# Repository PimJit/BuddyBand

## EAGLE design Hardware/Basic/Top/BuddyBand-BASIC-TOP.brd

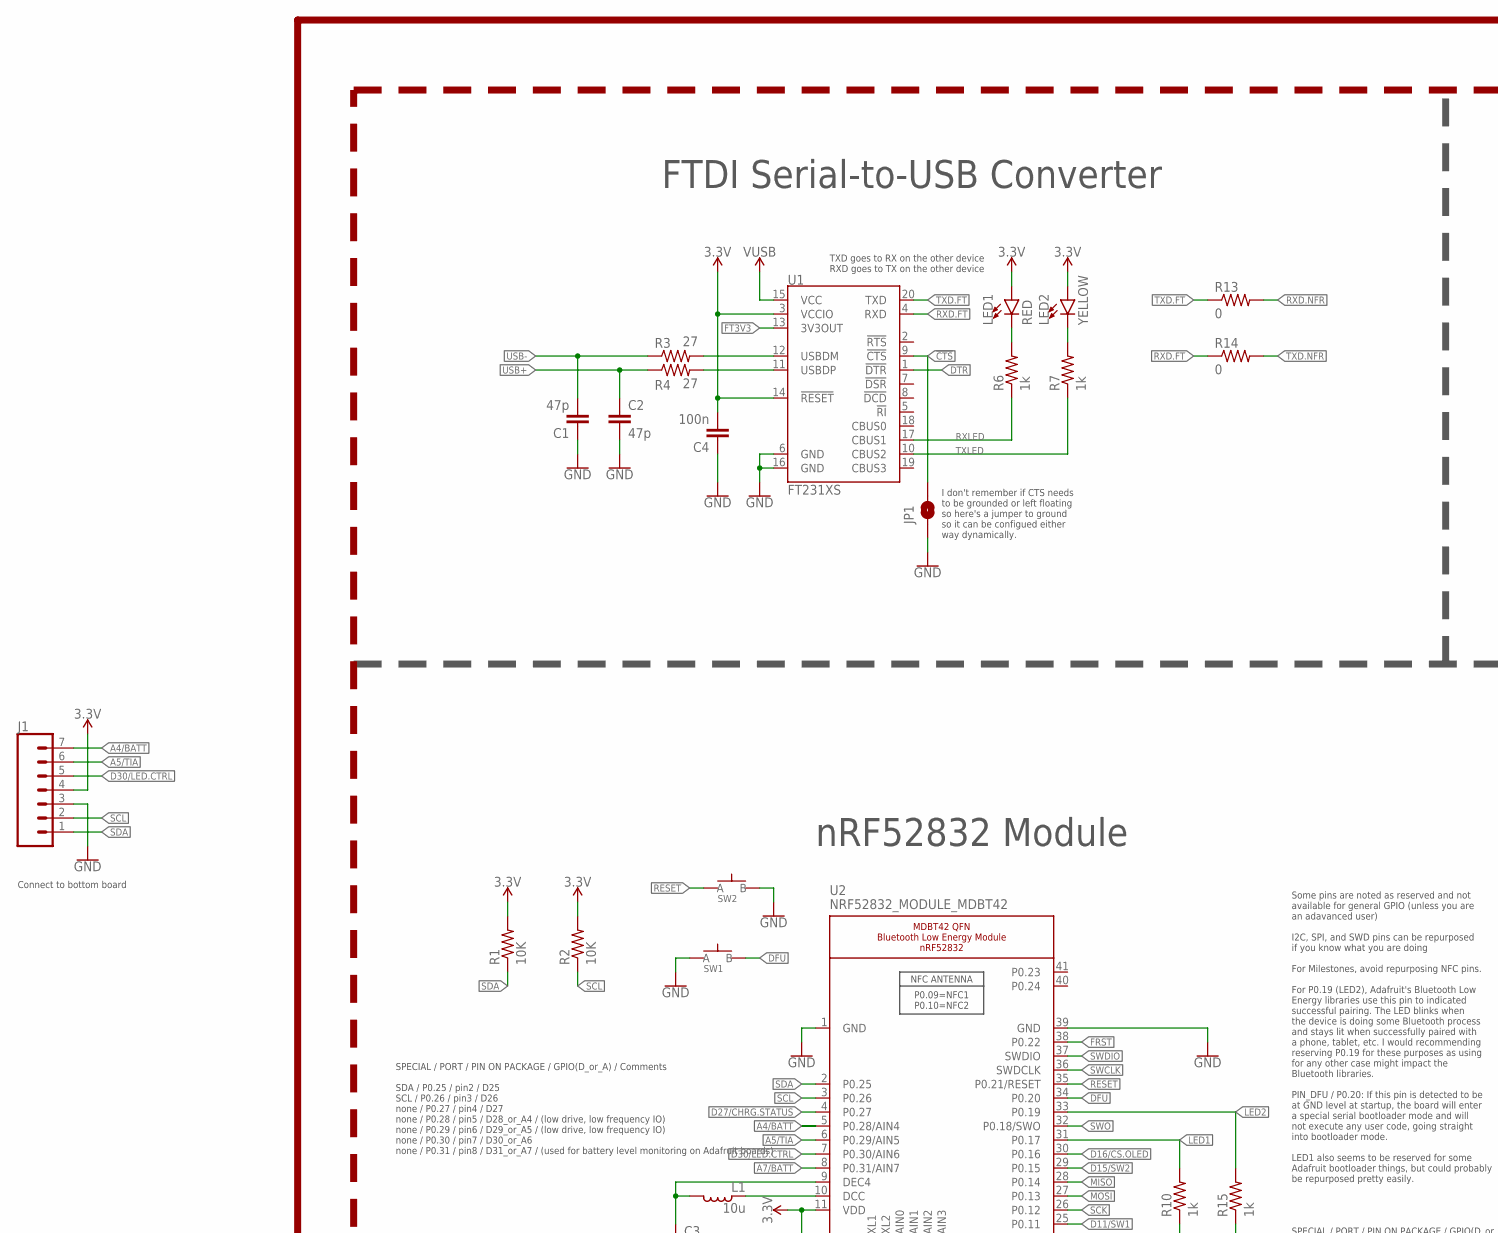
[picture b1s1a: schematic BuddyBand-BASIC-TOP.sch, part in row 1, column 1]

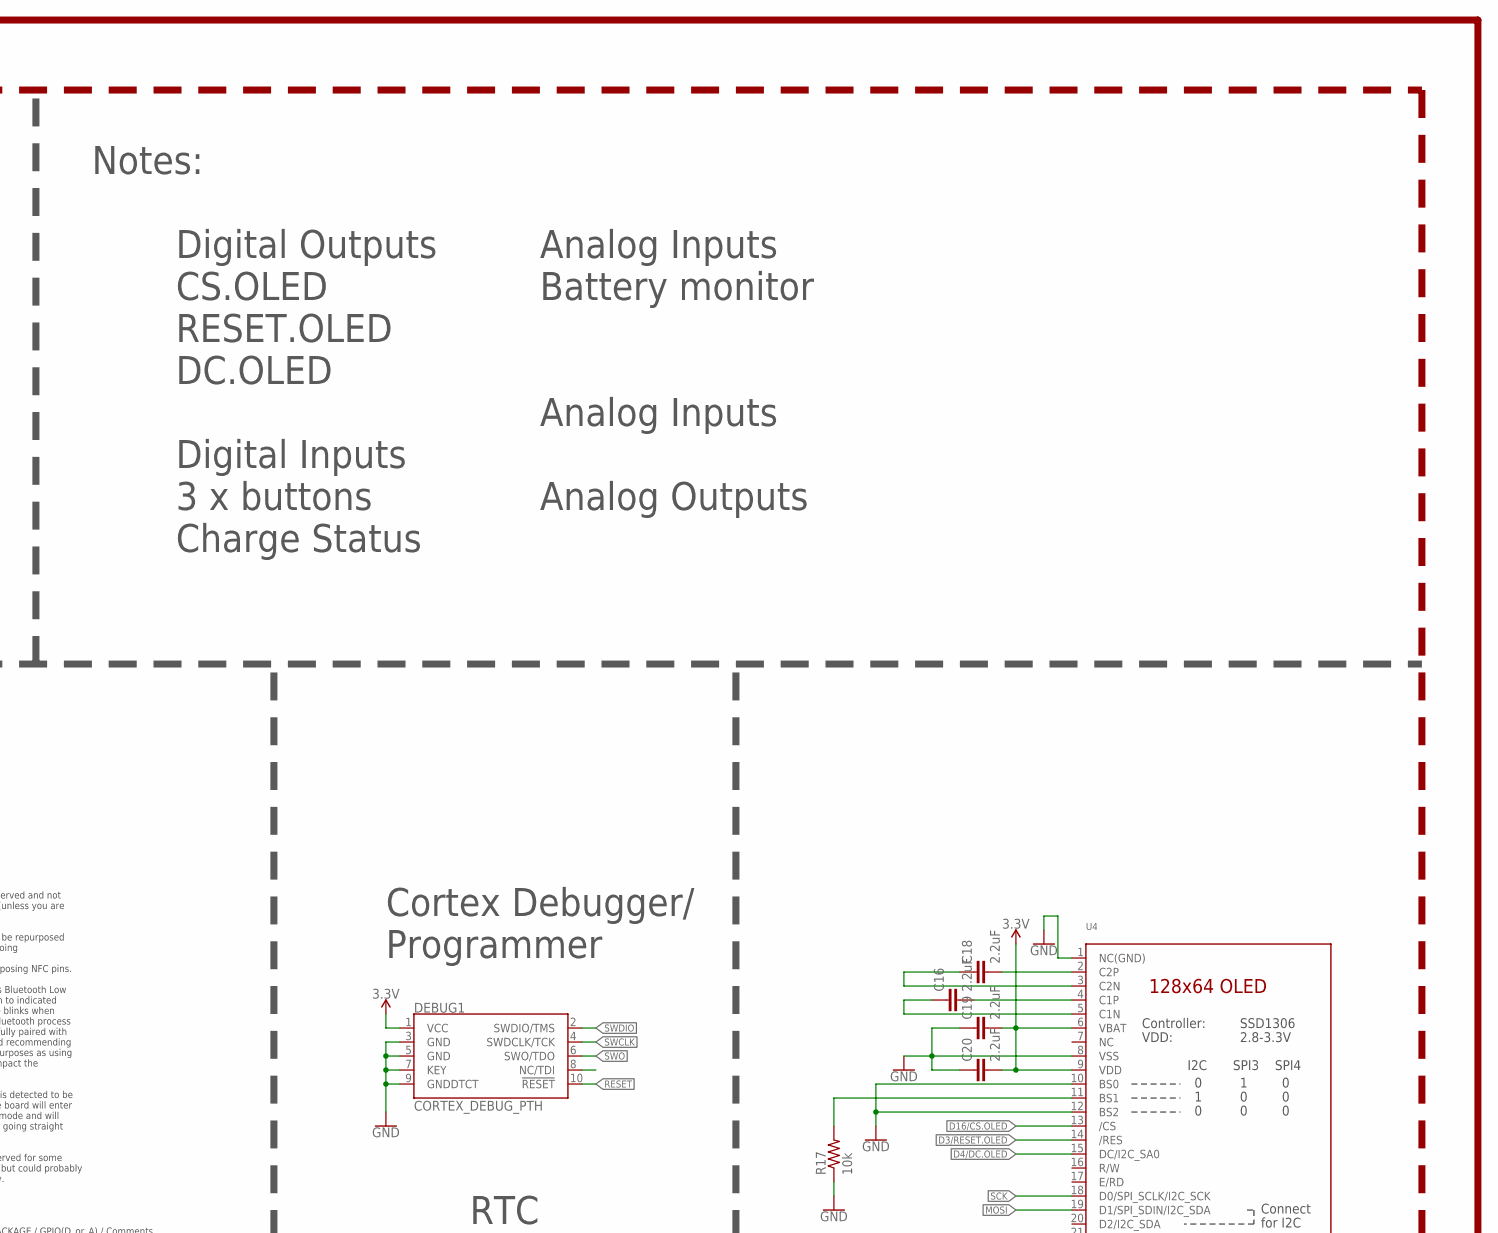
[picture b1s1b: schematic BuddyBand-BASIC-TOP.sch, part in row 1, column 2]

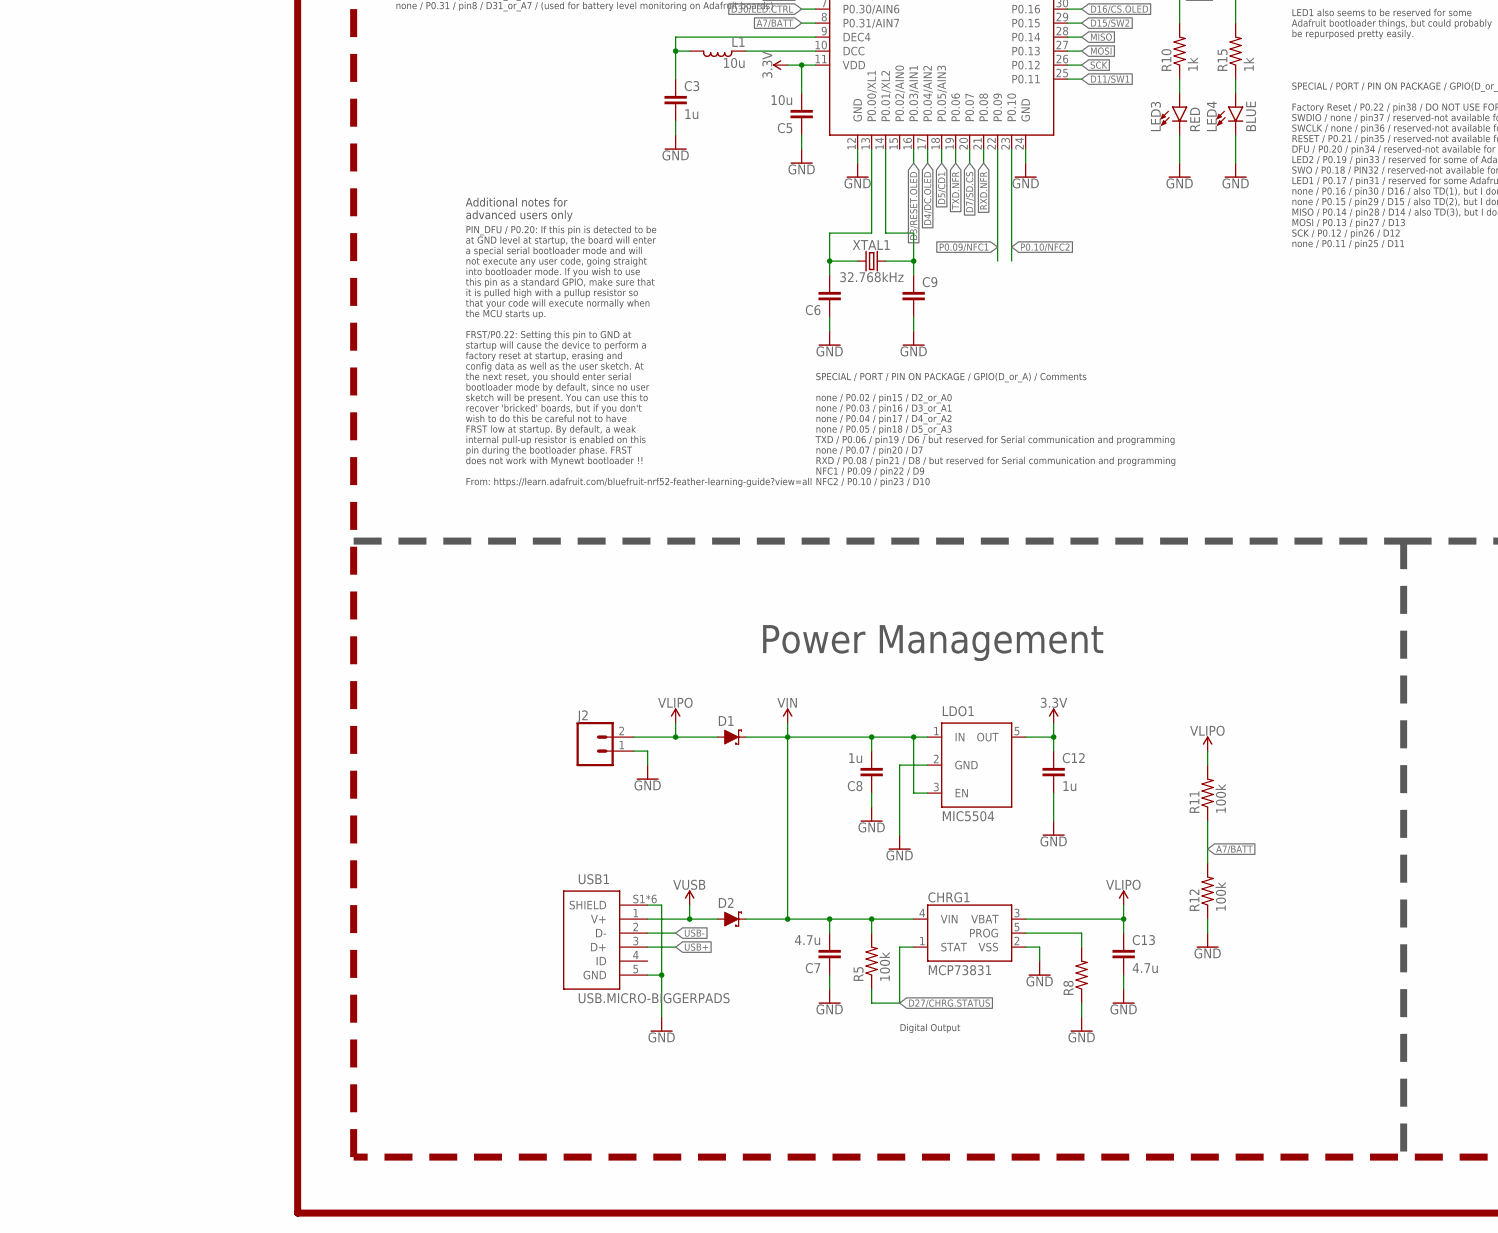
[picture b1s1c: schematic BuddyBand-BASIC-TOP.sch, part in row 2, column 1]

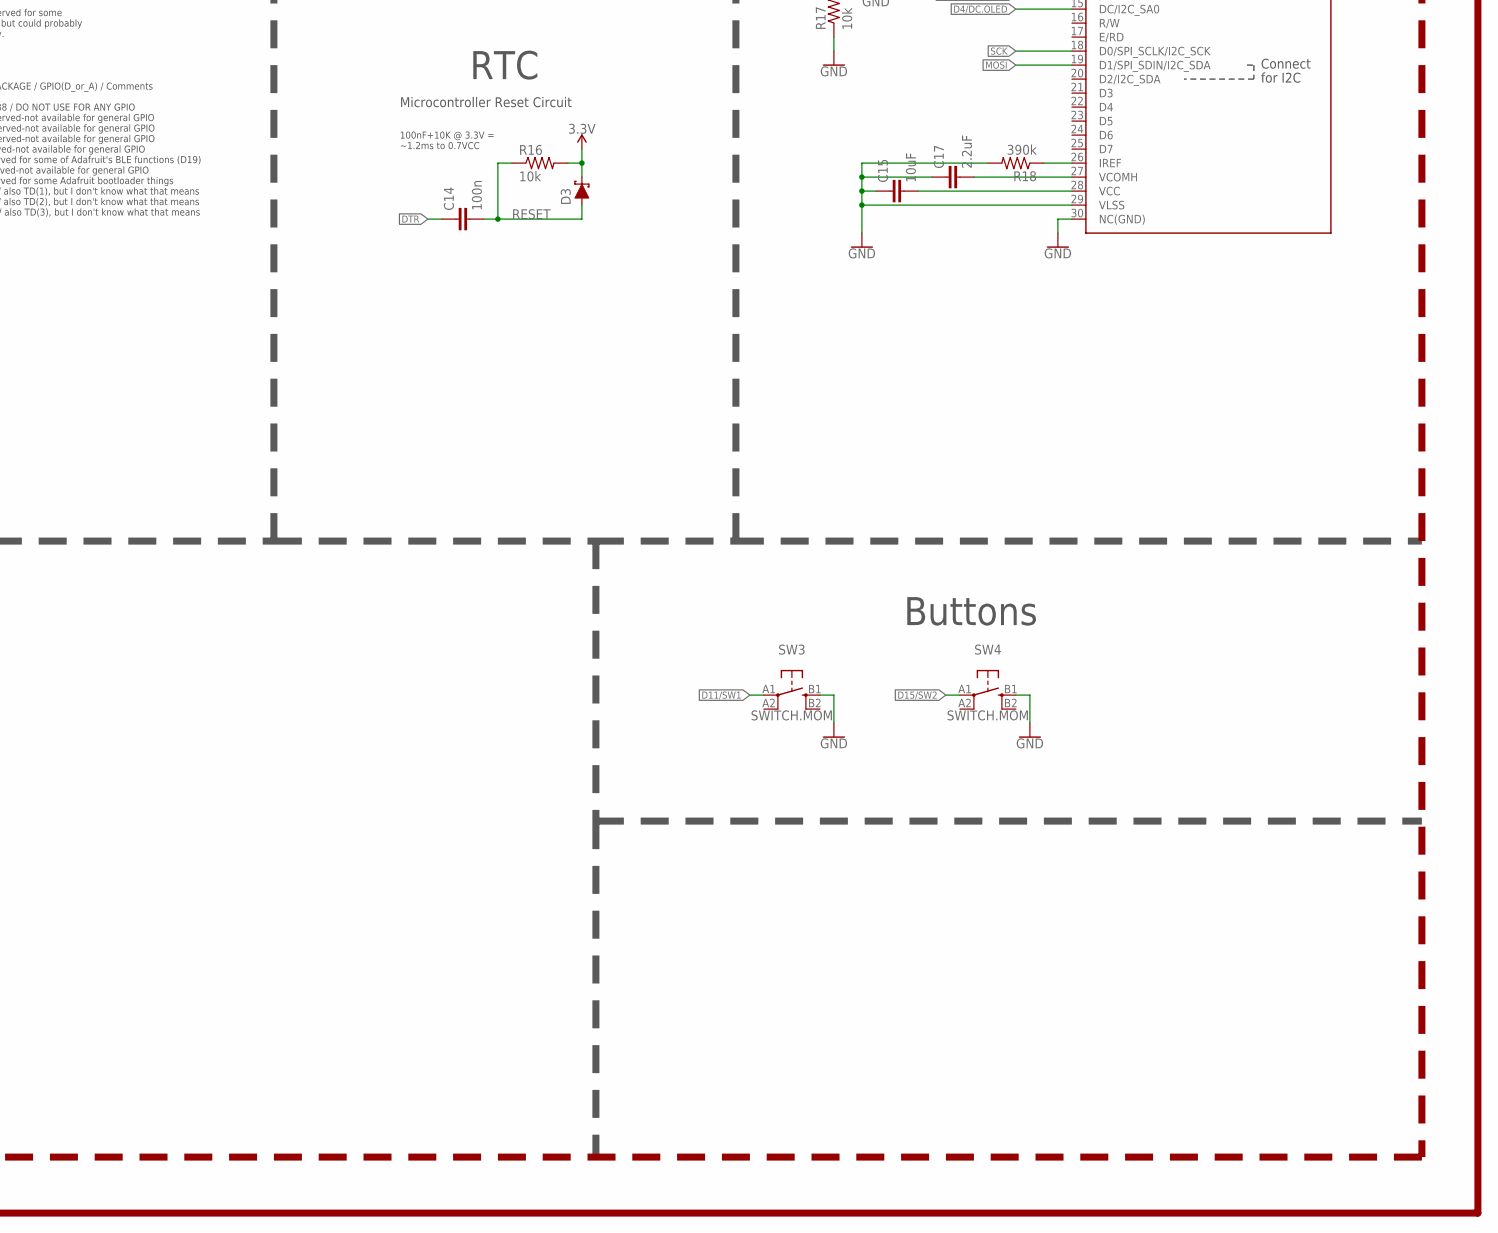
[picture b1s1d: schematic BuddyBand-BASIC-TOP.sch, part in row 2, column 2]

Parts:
C1, C2: 47p; C0603
C3, C8, C12: 1u; C0603
C4, C14: 100n; C0603
C5: 10u; C0805
C6, C9: CAPACITOR0603; C0603
C7, C13: 4.7u; C0603
C15: 10uF; C0603
C16, C17, C18, C19, C20: 2.2uF; C0402
CHRG1: MCP73831; SOT23-5
D1, D2, D3: SCHOTTKY-USC; USC
DEBUG1: CORTEX_DEBUG_PTH; 2X5-PTH-1.27MM
J1: CONN_07-1.27MM; 1X07_1.27MM
J2: CONN_02; 1X02
JP1: JUMPER-SMT_2_NO_SILK; SMT-JUMPER_2_NO_SILK
L1: 10u; L0603
LDO1: MIC5504; SOT23-5
LED1, LED3: RED; LED-0603
LED2: YELLOW; LED-0603
LED4: BLUE; LED-0603
R1, R2: 10K; R0603
R3, R4: 27; R0603
R5, R11, R12: 100k; R0603
R6, R7, R10, R15: 1k; R0603
R8: RESISTOR0603; R0603
R13, R14: 0; R0603
R16, R17: 10k; R0603
R18: 390k; R0603
SW1, SW2: SPST-PTS830GG140-COPY.1-3; BUTTON-GULLWING
SW3, SW4: SWITCH.MOM; TACTILE_SWITCH_SMD_6.2MM_TALL
U1: FT231XS; SSOP20_L
U2: NRF52832_MODULE_MDBT42; BLE_MODULE_RAYTAC_MDBT42
U4: DISP_OLED_UG-2864HSWEG01-NO-WRAPAROUND; UG-2864HSWEG01_0.96IN_NO-WRAPAROUND
USB1: USB.MICRO-BIGGERPADS; USB-MICRO-01.BIGGERPADS
XTAL1: 32.768kHz; 2-SMD.NOLEAD.2.0MMTO1.2MM

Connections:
3.3V: C4.2, C5.2, C12.1, C19.2, C20.2, D3.- (C), DEBUG1.1 (VCC), J1.4, LDO1.5 (OUT), LED1.A, LED2.A, R1.2, R2.2, R16.2, U1.3 (VCCIO), U1.14 (!RESET), U2.11 (VDD), U4.6 (VBAT), U4.9 (VDD)
!CTS: JP1.2, U1.9 (!CTS)
A4/BATT: J1.7, U2.5 (P0.28/AIN4)
A5/TIA: J1.6, U2.6 (P0.29/AIN5)
A7/BATT: R11.1, R12.2, U2.8 (P0.31/AIN7)
D3/RESET.OLED: U2.16 (P0.03/AIN1), U4.14 (/RES)
D4/DC.OLED: U2.17 (P0.04/AIN2), U4.15 (DC/I2C_SA0)
D5/CD1: U2.18 (P0.05/AIN3)
D7/SD.CS: U2.20 (P0.07)
D11/SW1: SW3.A1 (1), U2.25 (P0.11)
D15/SW2: SW4.A1 (1), U2.29 (P0.15)
D16/CS.OLED: U2.30 (P0.16), U4.13 (/CS)
D27/CHRG.STATUS: CHRG1.1 (STAT), R5.1, U2.4 (P0.27)
D30/LED.CTRL: J1.5, U2.7 (P0.30/AIN6)
DFU: SW1.3 (B), U2.34 (P0.20)
DTR: C14.1, U1.1 (!DTR)
FRST: U2.38 (P0.22)
FT3V3: U1.13 (3V3OUT)
GND: C1.1, C2.2, C3.2, C4.1, C5.1, C6.1, C7.1, C8.1, C9.2, C12.2, C13.2, C15.1, C17.1, C19.1, C20.1, CHRG1.2 (VSS), DEBUG1.3 (GND), DEBUG1.5 (GND), DEBUG1.7 (KEY), DEBUG1.9 (GNDDTCT), J1.3, J2.1, JP1.1, LDO1.2 (GND), LED3.C, LED4.C, R8.1, R12.1, R17.1, R18.2, SW1.1 (A), SW2.3 (B), SW3.B1 (3), SW4.B1 (3), U1.6 (GND), U1.16 (GND), U2.1 (GND), U2.12 (GND), U2.24 (GND), U2.39 (GND), U4.1 (NC(GND)), U4.8 (VSS), U4.10 (BS0), U4.12 (BS2), U4.29 (VLSS), U4.30 (NC(GND)), USB1.5 (GND), USB1.S1 (SHIELD), USB1.S2 (SHIELD), USB1.S3 (SHIELD), USB1.S4 (SHIELD), USB1.S5 (SHIELD), USB1.S6 (SHIELD)
LED1: R10.2, U2.31 (P0.17)
LED2: R15.2, U2.33 (P0.19)
MISO: U2.28 (P0.14)
MOSI: U2.27 (P0.13), U4.19 (D1/SPI_SDIN/I2C_SDA)
unnamed: R17.2, U4.11 (BS1)
unnamed: R18.1, U4.26 (IREF)
unnamed: C18.2, U4.2 (C2P)
unnamed: C6.2, U2.13 (P0.00/XL1), XTAL1.P$1 (1)
unnamed: C18.1, U4.3 (C2N)
unnamed: C9.1, U2.14 (P0.01/XL2), XTAL1.P$2 (2)
unnamed: C16.2, U4.4 (C1P)
unnamed: C16.1, U4.5 (C1N)
unnamed: LED3.A, R10.1
unnamed: LED4.A, R15.1
unnamed: L1.1, U2.10 (DCC)
unnamed: C3.1, L1.2, U2.9 (DEC4)
unnamed: C15.2, U4.28 (VCC)
unnamed: C17.2, U4.27 (VCOMH)
unnamed: CHRG1.5 (PROG), R8.2
unnamed: R3.2, U1.12 (USBDM)
unnamed: R4.2, U1.11 (USBDP)
unnamed: LED1.C, R6.2
unnamed: LED2.C, R7.2
P0.09/NFC1: U2.22 (P0.09)
P0.10/NFC2: U2.23 (P0.10)
RESET: C14.2, D3.+ (A), DEBUG1.10 (!RESET), R16.1, SW2.1 (A), U2.35 (P0.21/RESET)
RXD.FT: R14.1, U1.4 (RXD)
RXD.NFR: R13.2, U2.21 (P0.08)
RXLED: R6.1, U1.17 (CBUS1)
SCK: U2.26 (P0.12), U4.18 (D0/SPI_SCLK/I2C_SCK)
SCL: J1.2, R2.1, U2.3 (P0.26)
SDA: J1.1, R1.1, U2.2 (P0.25)
SWCLK: DEBUG1.4 (SWDCLK/TCK), U2.36 (SWDCLK)
SWDIO: DEBUG1.2 (SWDIO/TMS), U2.37 (SWDIO)
SWO: DEBUG1.6 (SWO/TDO), U2.32 (P0.18/SWO)
TXD.FT: R13.1, U1.20 (TXD)
TXD.NFR: R14.2, U2.19 (P0.06)
TXLED: R7.1, U1.10 (CBUS2)
USB+: C2.1, R4.1, USB1.3 (D+)
USB-: C1.2, R3.1, USB1.2 (D-)
VIN: C7.2, C8.2, CHRG1.4 (VIN), D1.- (C), D2.- (C), LDO1.1 (IN), LDO1.3 (EN), R5.2
VLIPO: C13.1, CHRG1.3 (VBAT), D1.+ (A), J2.2, R11.2
V_USB: D2.+ (A), U1.15 (VCC), USB1.1 (V+)

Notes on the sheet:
Microcontroller Reset Circuit
100nF+10K @ 3.3V = ~1.2ms to 0.7VCC
SPECIAL / PORT / PIN ON PACKAGE / GPIO(D_or_A) / Comments SDA / P0.25 / pin2 / D25 SCL / P0.26 / pin3 / D26 none / P0.27 / pin4 / D27 none / P0.28 / pin5 / D28_or_A4 / (low drive, low frequency IO) none / P0.29 / pin6 / D29_or_A5 / (low drive, low frequency IO) none / P0.30 / pin7 / D30_or_A6 none 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
SPECIAL / PORT / PIN ON PACKAGE / GPIO(D_or_A) / Comments none / P0.02 / pin15 / D2_or_A0 none / P0.03 / pin16 / D3_or_A1 none / P0.04 / pin17 / D4_or_A2 none / P0.05 / pin18 / D5_or_A3 TXD / P0.06 / pin19 / D6 / but reserved for Serial communication and programming none / P0.07 / pin20 / D7 RXD / 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
SPECIAL / PORT / PIN ON PACKAGE / GPIO(D_or_A) / Comments Factory Reset / P0.22 / pin38 / DO NOT USE FOR ANY GPIO SWDIO / none / pin37 / reserved-not available for general GPIO SWCLK / none / pin36 / reserved-not available for general GPIO RESET / P0.21 / pin35 / reserved-not available for general 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
Some pins are noted as reserved and not available for general GPIO (unless you are an adavanced user) I2C, SPI, and SWD pins can be repurposed if you know what you are doing For Milestones, avoid repurposing NFC pins. For P0.19 (LED2), Adafruit's Bluetooth Low Energy libraries use this pin to indic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
PIN_DFU / P0.20: If this pin is detected to be at GND level at startup, the board will enter a special serial bootloader mode and will not execute any user code, going straight into bootloader mode. If you wish to use this pin as a standard GPIO, make sure that it is pulled high with a pullup resis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
Additional notes for advanced users only
nRF52832 Module
Buttons
Power Management
Cortex Debugger/ Programmer
RTC
Analog Inputs Battery monitor Analog Inputs Analog Outputs
TXD goes to RX on the other device RXD goes to TX on the other device
I don't remember if CTS needs to be grounded or left floating so here's a jumper to ground so it can be configued either way dynamically.
FTDI Serial-to-USB Converter
Notes:
Digital Outputs CS.OLED RESET.OLED DC.OLED Digital Inputs 3 x buttons Charge Status
Digital Output
Connect to bottom board

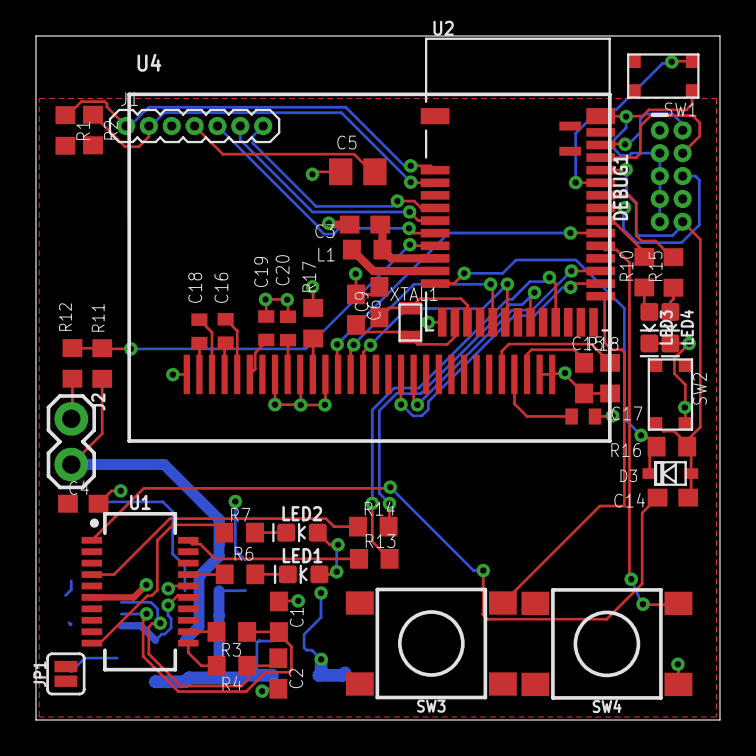
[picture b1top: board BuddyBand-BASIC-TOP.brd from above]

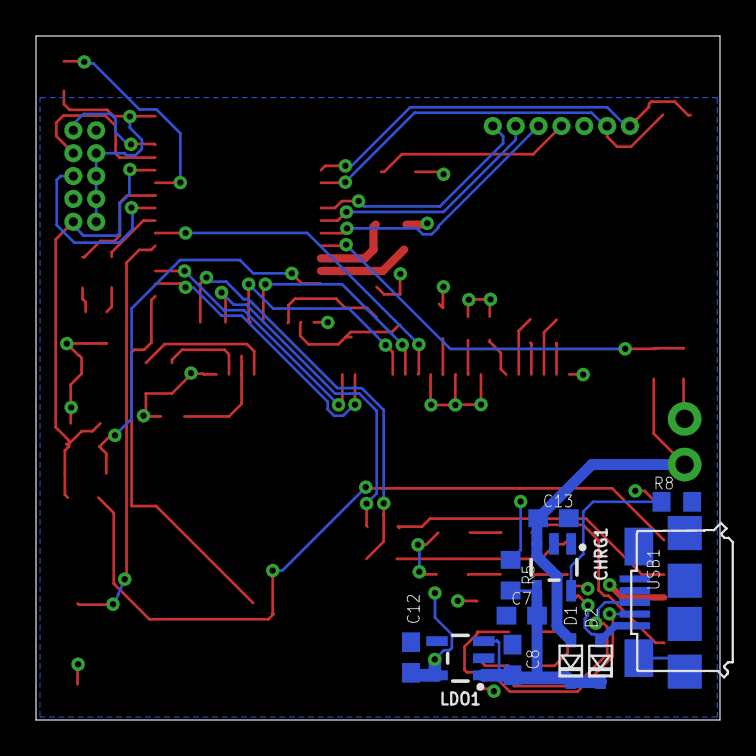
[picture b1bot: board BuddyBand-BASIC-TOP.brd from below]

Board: 2 copper layers, 38.0 x 38.0 mm, 58 parts (11 on the bottom side), 55 nets.

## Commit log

2020-07-07 added blank arduino file
2020-07-07 added document on describing what BuddyBand will do and some other things includes such as questions regarding the making of it and its purpose.
2020-07-07 Added collaborators
2020-07-09 Finished top board from first video.
2020-07-14 In process of working on Take 003 video.
2020-07-21 Finished take 5 working on take 6
2020-07-28 doing take 7. have trouble with wiring
